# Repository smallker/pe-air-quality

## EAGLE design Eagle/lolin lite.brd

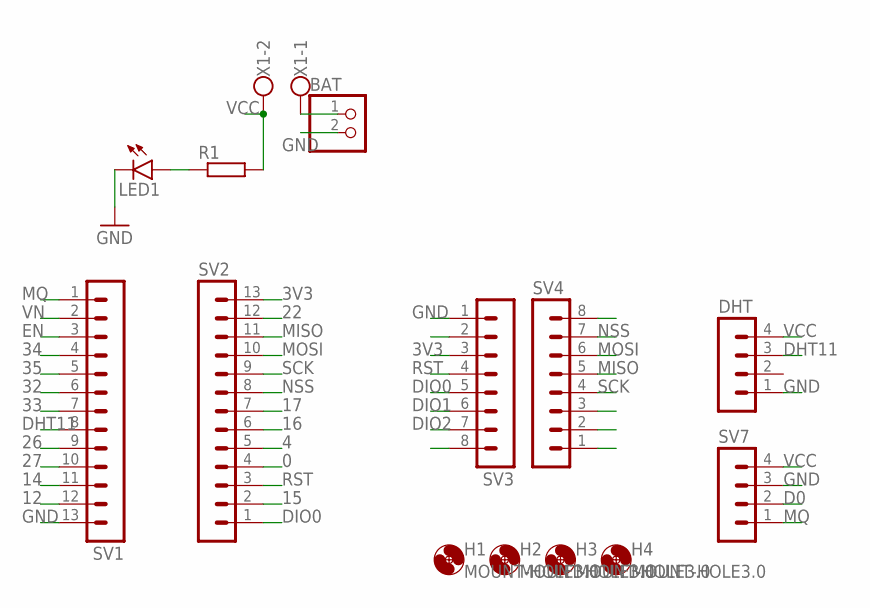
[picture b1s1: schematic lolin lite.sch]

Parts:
BAT: PINHD-1X2; 1X02
DHT: MA04-1
H1, H2, H3, H4: MOUNT-HOLE3.0; 3,0
LED1: LED5MM
R1: R-EU_0309/10; 0309/10
SV1, SV2: MA13-1
SV3, SV4: MA08-1
SV7: MA04-1
X1: W237-102

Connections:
0: SV2.4
3V3: SV2.13, SV3.3
4: SV2.5
12: SV1.12
14: SV1.11
15: SV2.2
16: SV2.6
17: SV2.7
22: SV2.12
26: SV1.9
27: SV1.10
32: SV1.6
33: SV1.7
34: SV1.4
35: SV1.5
D0: SV7.2
DHT11: DHT.3, SV1.8
DIO0: SV2.1, SV3.5
DIO1: SV3.6
DIO2: SV3.7
EN: SV1.3
GND: BAT.2, DHT.1, LED1.K (C), SV1.13, SV3.1, SV7.3
MISO: SV2.11, SV4.5
MOSI: SV2.10, SV4.6
MQ: SV1.1, SV7.1
unnamed: LED1.A, R1.1
unnamed: BAT.1, X1.1
NSS: SV2.8, SV4.7
RST: SV2.3, SV3.4
SCK: SV2.9, SV4.4
VCC: DHT.4, R1.2, SV7.4, X1.2
VN: SV1.2

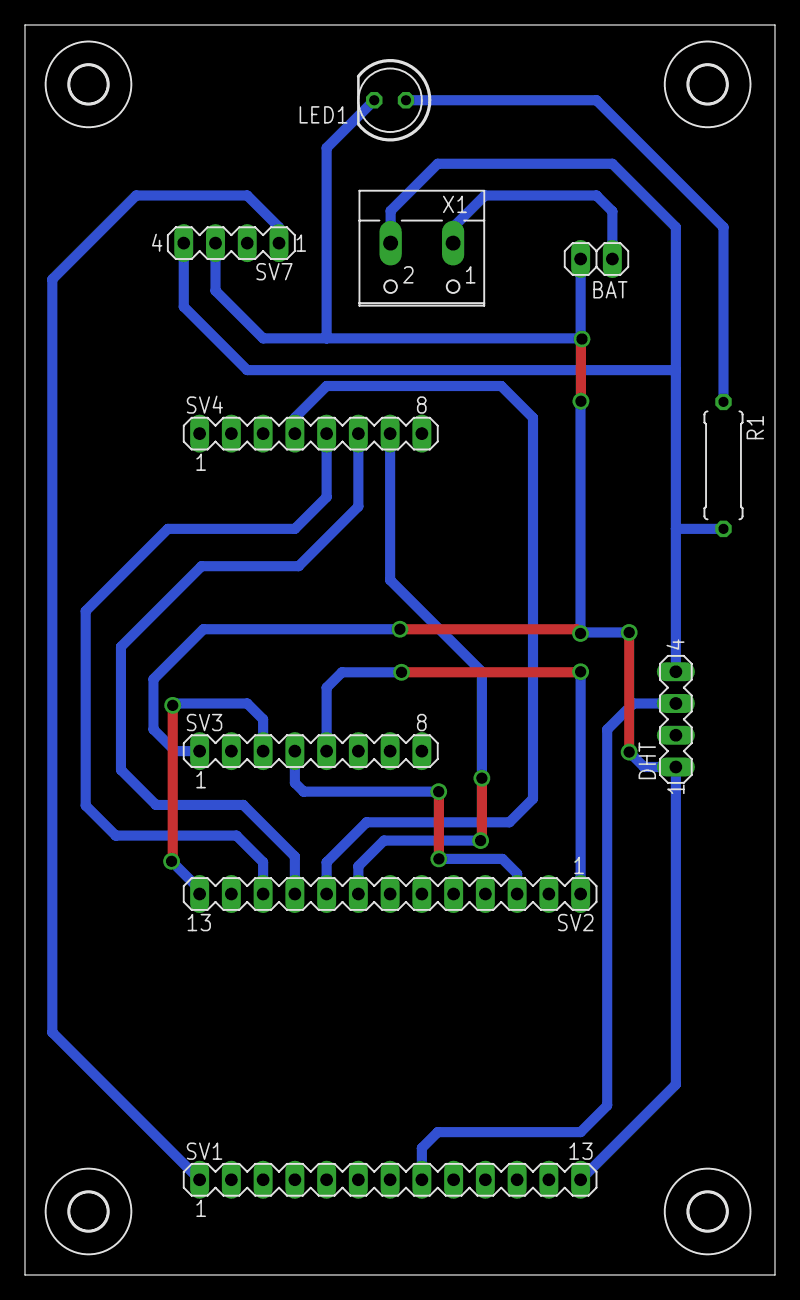
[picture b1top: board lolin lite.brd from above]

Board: 2 copper layers, 60.0 x 100.0 mm, 14 parts (0 on the bottom side), 13 nets.

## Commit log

2020-10-21 UI done
2020-11-13 latest 13 nov 2020
2020-11-14 wes iso ngirim ng firebase
2020-11-14 fix kabeh
2020-11-16 layout
2020-11-17 add eagle schema, layout
2020-11-17 bismillah
2020-11-18 trouble sitik
2020-11-19 bismillah sangar
2020-11-25 wes bar
